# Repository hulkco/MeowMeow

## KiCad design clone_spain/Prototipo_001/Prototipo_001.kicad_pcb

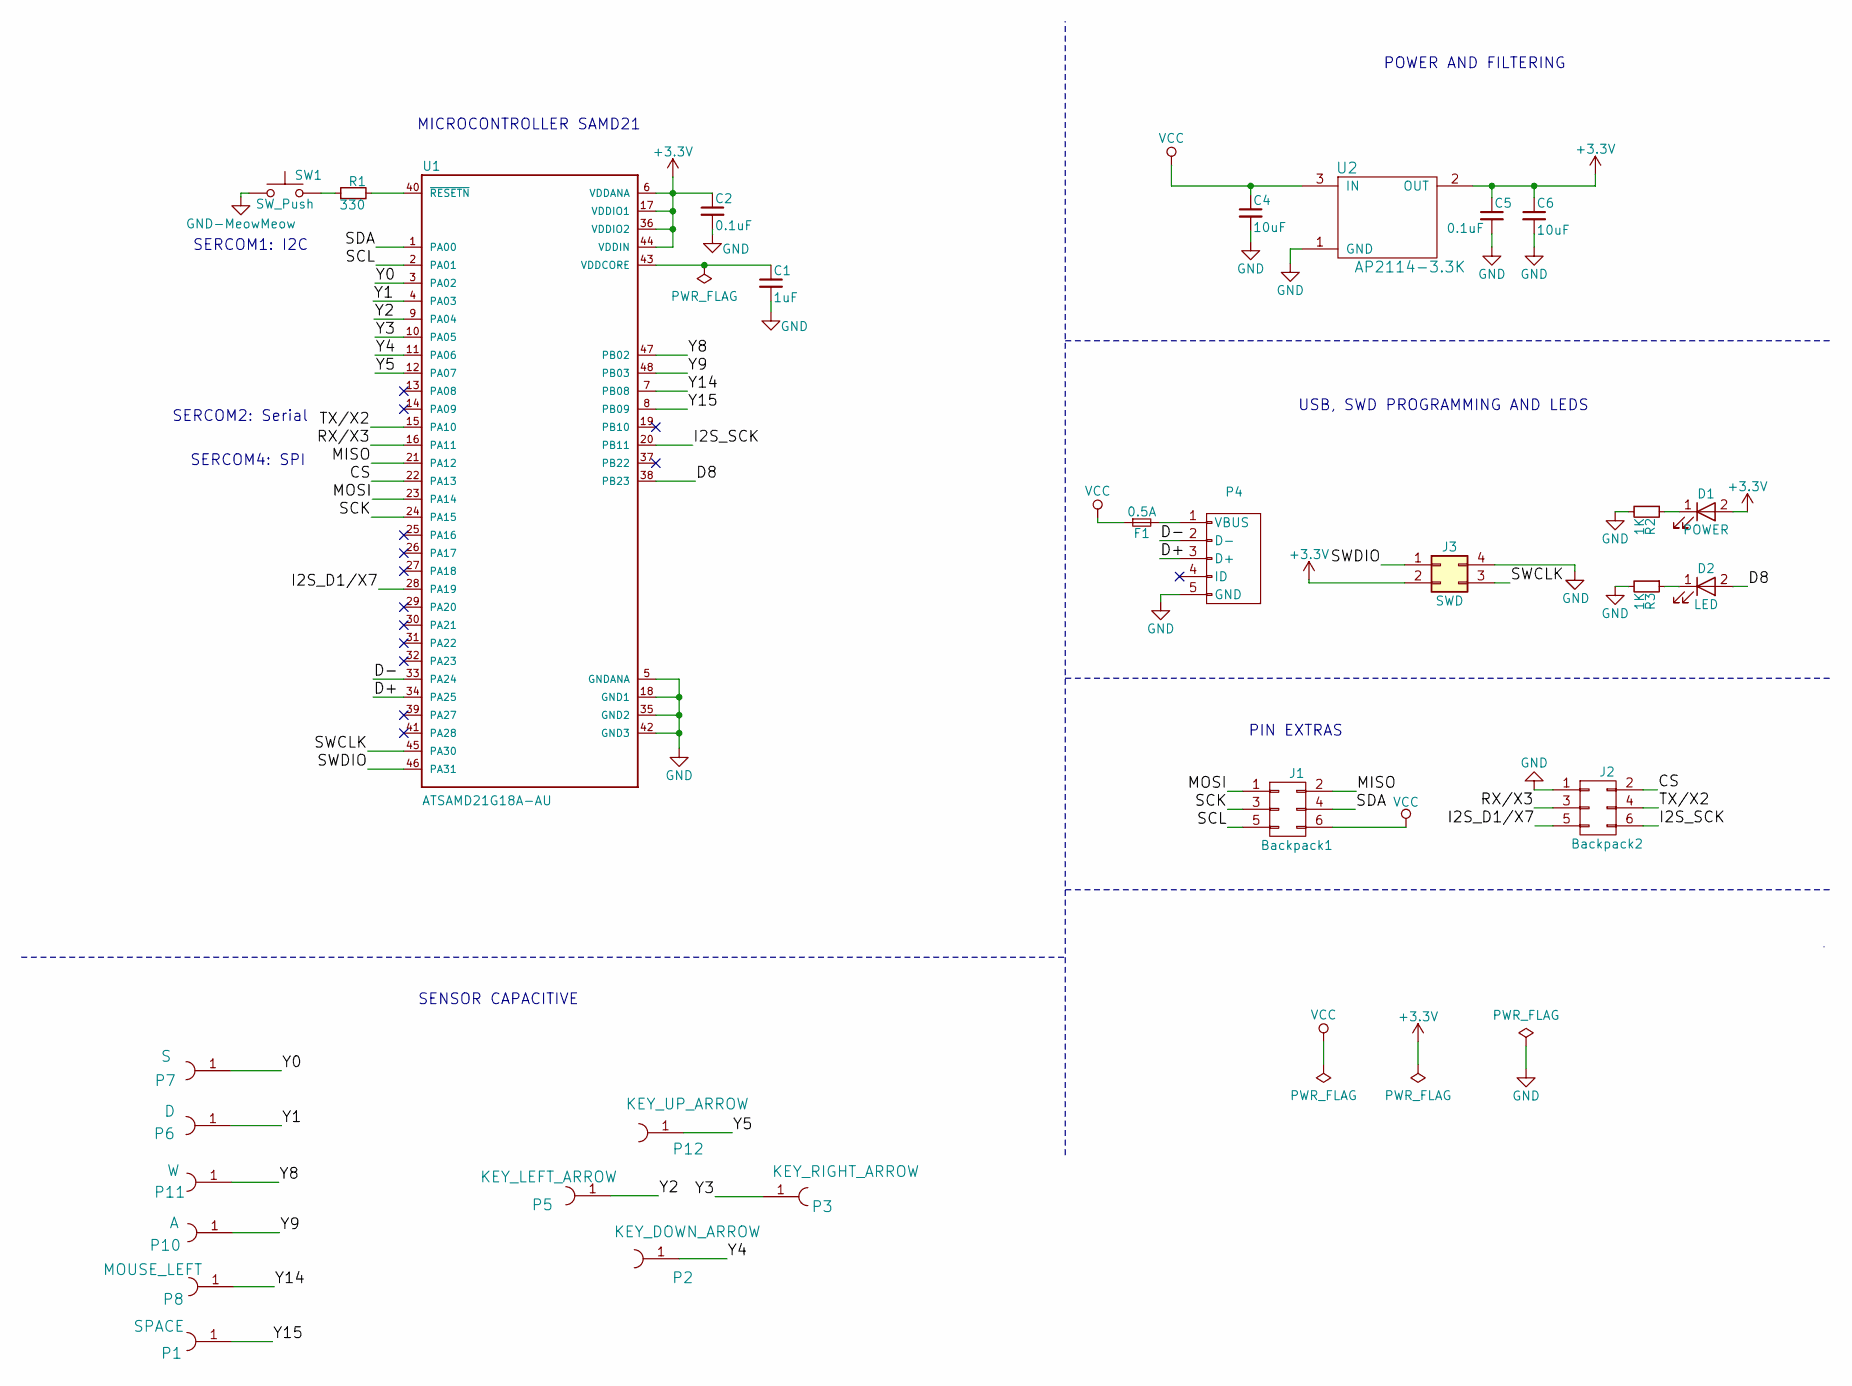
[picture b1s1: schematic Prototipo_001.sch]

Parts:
C1: 1uF; C_0805_HandSoldering; Part# C2012X7R1C105K125AA
C2, C5: 0.1uF; C_0805_HandSoldering; Part# 885012207072
C4, C6: 10uF; C_0805_HandSoldering; Part# TMCUA0J106MTR2F
D1: POWER; LED_0805_HandSoldering; Part# APT2012SGC
D2: LED; LED_0805_HandSoldering; Part# APT2012SGC
F1: 0.5A; R_1812_HandSoldering; Part# 0ZCG0030FF2C
J1: Backpack1; Pin_Header_Straight_2x03_Pitch2.54mm_SMD
J2: Backpack2; Pin_Header_Straight_2x03_Pitch2.54mm_SMD
J3: SWD; Pin_Header_Straight_2x02_Pitch2.54mm_SMD
P1: SPACE; Caiman_Conn
P2: KEY_DOWN_ARROW; Caiman_Conn
P3: KEY_RIGHT_ARROW; Caiman_Conn
P4: USB_5_Pin-MeowMeow; USB_Micro-B_Wuerth_629105150521
P5: KEY_LEFT_ARROW; Caiman_Conn
P6: D; Caiman_Conn
P7: S; Caiman_Conn
P8: MOUSE_LEFT; Caiman_Conn
P10: A; Caiman_Conn
P11: W; Caiman_Conn
P12: KEY_UP_ARROW; Caiman_Conn
R1: 330; R_0805_HandSoldering; Part# B3U-1000P
R2, R3: 1K; R_0805_HandSoldering; Part# AC0805FR-071KL
SW1: SW_Push; SW_SPST_TL3342
U1: ATSAMD21G18A-AU; TQFP-48_7x7mm_Pitch0.5mm; Part# ATSAMD21G15A-AU
U2: AP2114-3.3K; SOT-223-3Lead_TabPin2; Part# AP2114H-3.3TRG1

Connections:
+3V3: C2.1, C5.1, C6.1, D1.2 (A), J3.2, U1.6 (VDDANA), U1.17 (VDDIO1), U1.36 (VDDIO2), U1.44 (VDDIN), U2.2 (OUT)
/CS: J2.2, U1.22 (PA13)
/D8: D2.2 (A), U1.38 (PB23)
/D+: P4.3 (D+), U1.34 (PA25)
/D-: P4.2 (D-), U1.33 (PA24)
/I2S_D1/X7: J2.5, U1.28 (PA19)
/I2S_SCK: J2.6, U1.20 (PB11)
/MISO: J1.2, U1.21 (PA12)
/MOSI: J1.1, U1.23 (PA14)
/RX/X3: J2.3, U1.16 (PA11)
/SCK: J1.3, U1.24 (PA15)
/SCL: J1.5, U1.2 (PA01)
/SDA: J1.4, U1.1 (PA00)
/SWCLK: J3.3, U1.45 (PA30)
/SWDIO: J3.1, U1.46 (PA31)
/TX/X2: J2.4, U1.15 (PA10)
/Y0: P7.1, U1.3 (PA02)
/Y1: P6.1, U1.4 (PA03)
/Y2: P5.1, U1.9 (PA04)
/Y3: P3.1, U1.10 (PA05)
/Y4: P2.1, U1.11 (PA06)
/Y5: P12.1, U1.12 (PA07)
/Y8: P11.1, U1.47 (PB02)
/Y9: P10.1, U1.48 (PB03)
/Y14: P8.1, U1.7 (PB08)
/Y15: P1.1, U1.8 (PB09)
unnamed: C1.1, U1.43 (VDDCORE)
unnamed: D1.1 (K), R2.1
unnamed: D2.1 (K), R3.1
unnamed: F1.2, P4.1 (VBUS)
unnamed: R1.1, SW1.2
unnamed: R1.2, U1.40 (~RESETN~)
VCC: C4.1, F1.1, J1.6, U2.3 (IN)

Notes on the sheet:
MICROCONTROLLER SAMD21
POWER AND FILTERING
USB, SWD PROGRAMMING AND LEDS
SENSOR CAPACITIVE
SERCOM4: SPI
SERCOM1: I2C
SERCOM2: Serial
PIN EXTRAS

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
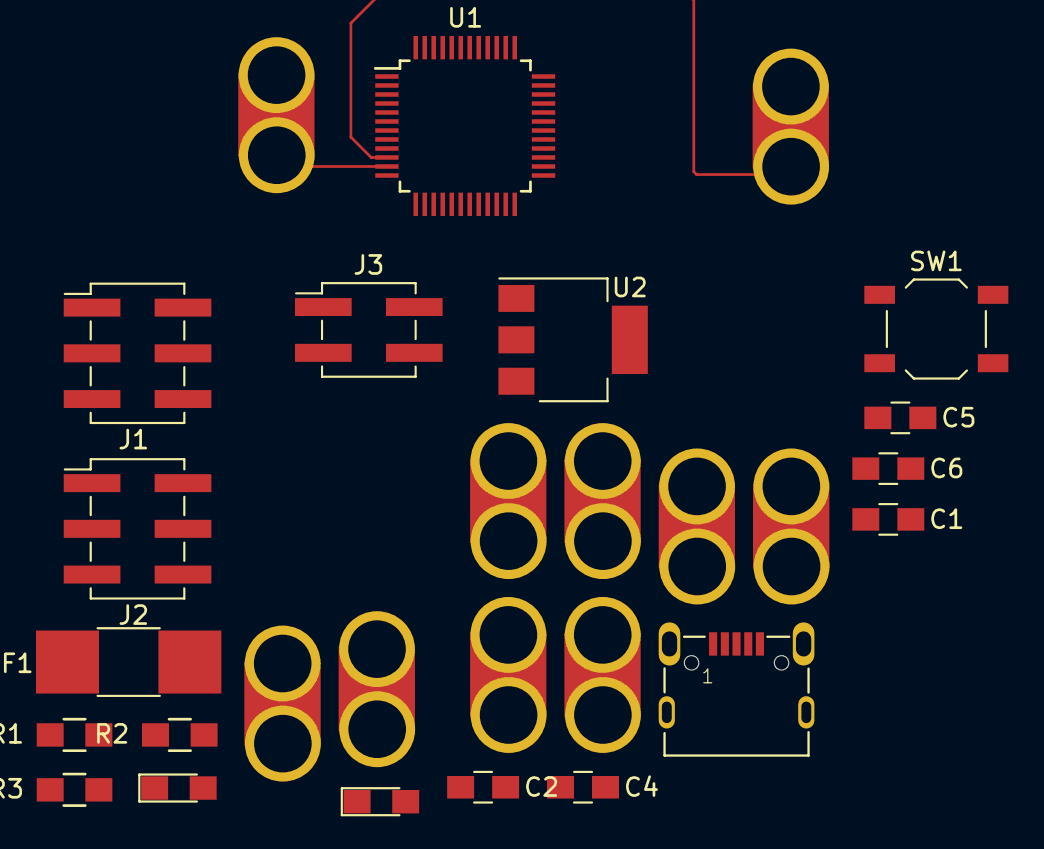
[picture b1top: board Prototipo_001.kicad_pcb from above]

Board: 2 copper layers, 28 parts (0 on the bottom side), 34 nets.

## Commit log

2020-01-08 update GND
2020-01-10 Add new project
2020-01-13 Add paso footprint
2020-01-13 Some minors update paso
2020-01-14 minor update
2020-01-15 Auto stash before merge of "master" and "origin/master"
2020-01-15 Add ADC Nano
2020-01-22 Clear
